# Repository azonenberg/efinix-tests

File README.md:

# efinix-tests
Miscellaneous experiments with Efinix FPGAs

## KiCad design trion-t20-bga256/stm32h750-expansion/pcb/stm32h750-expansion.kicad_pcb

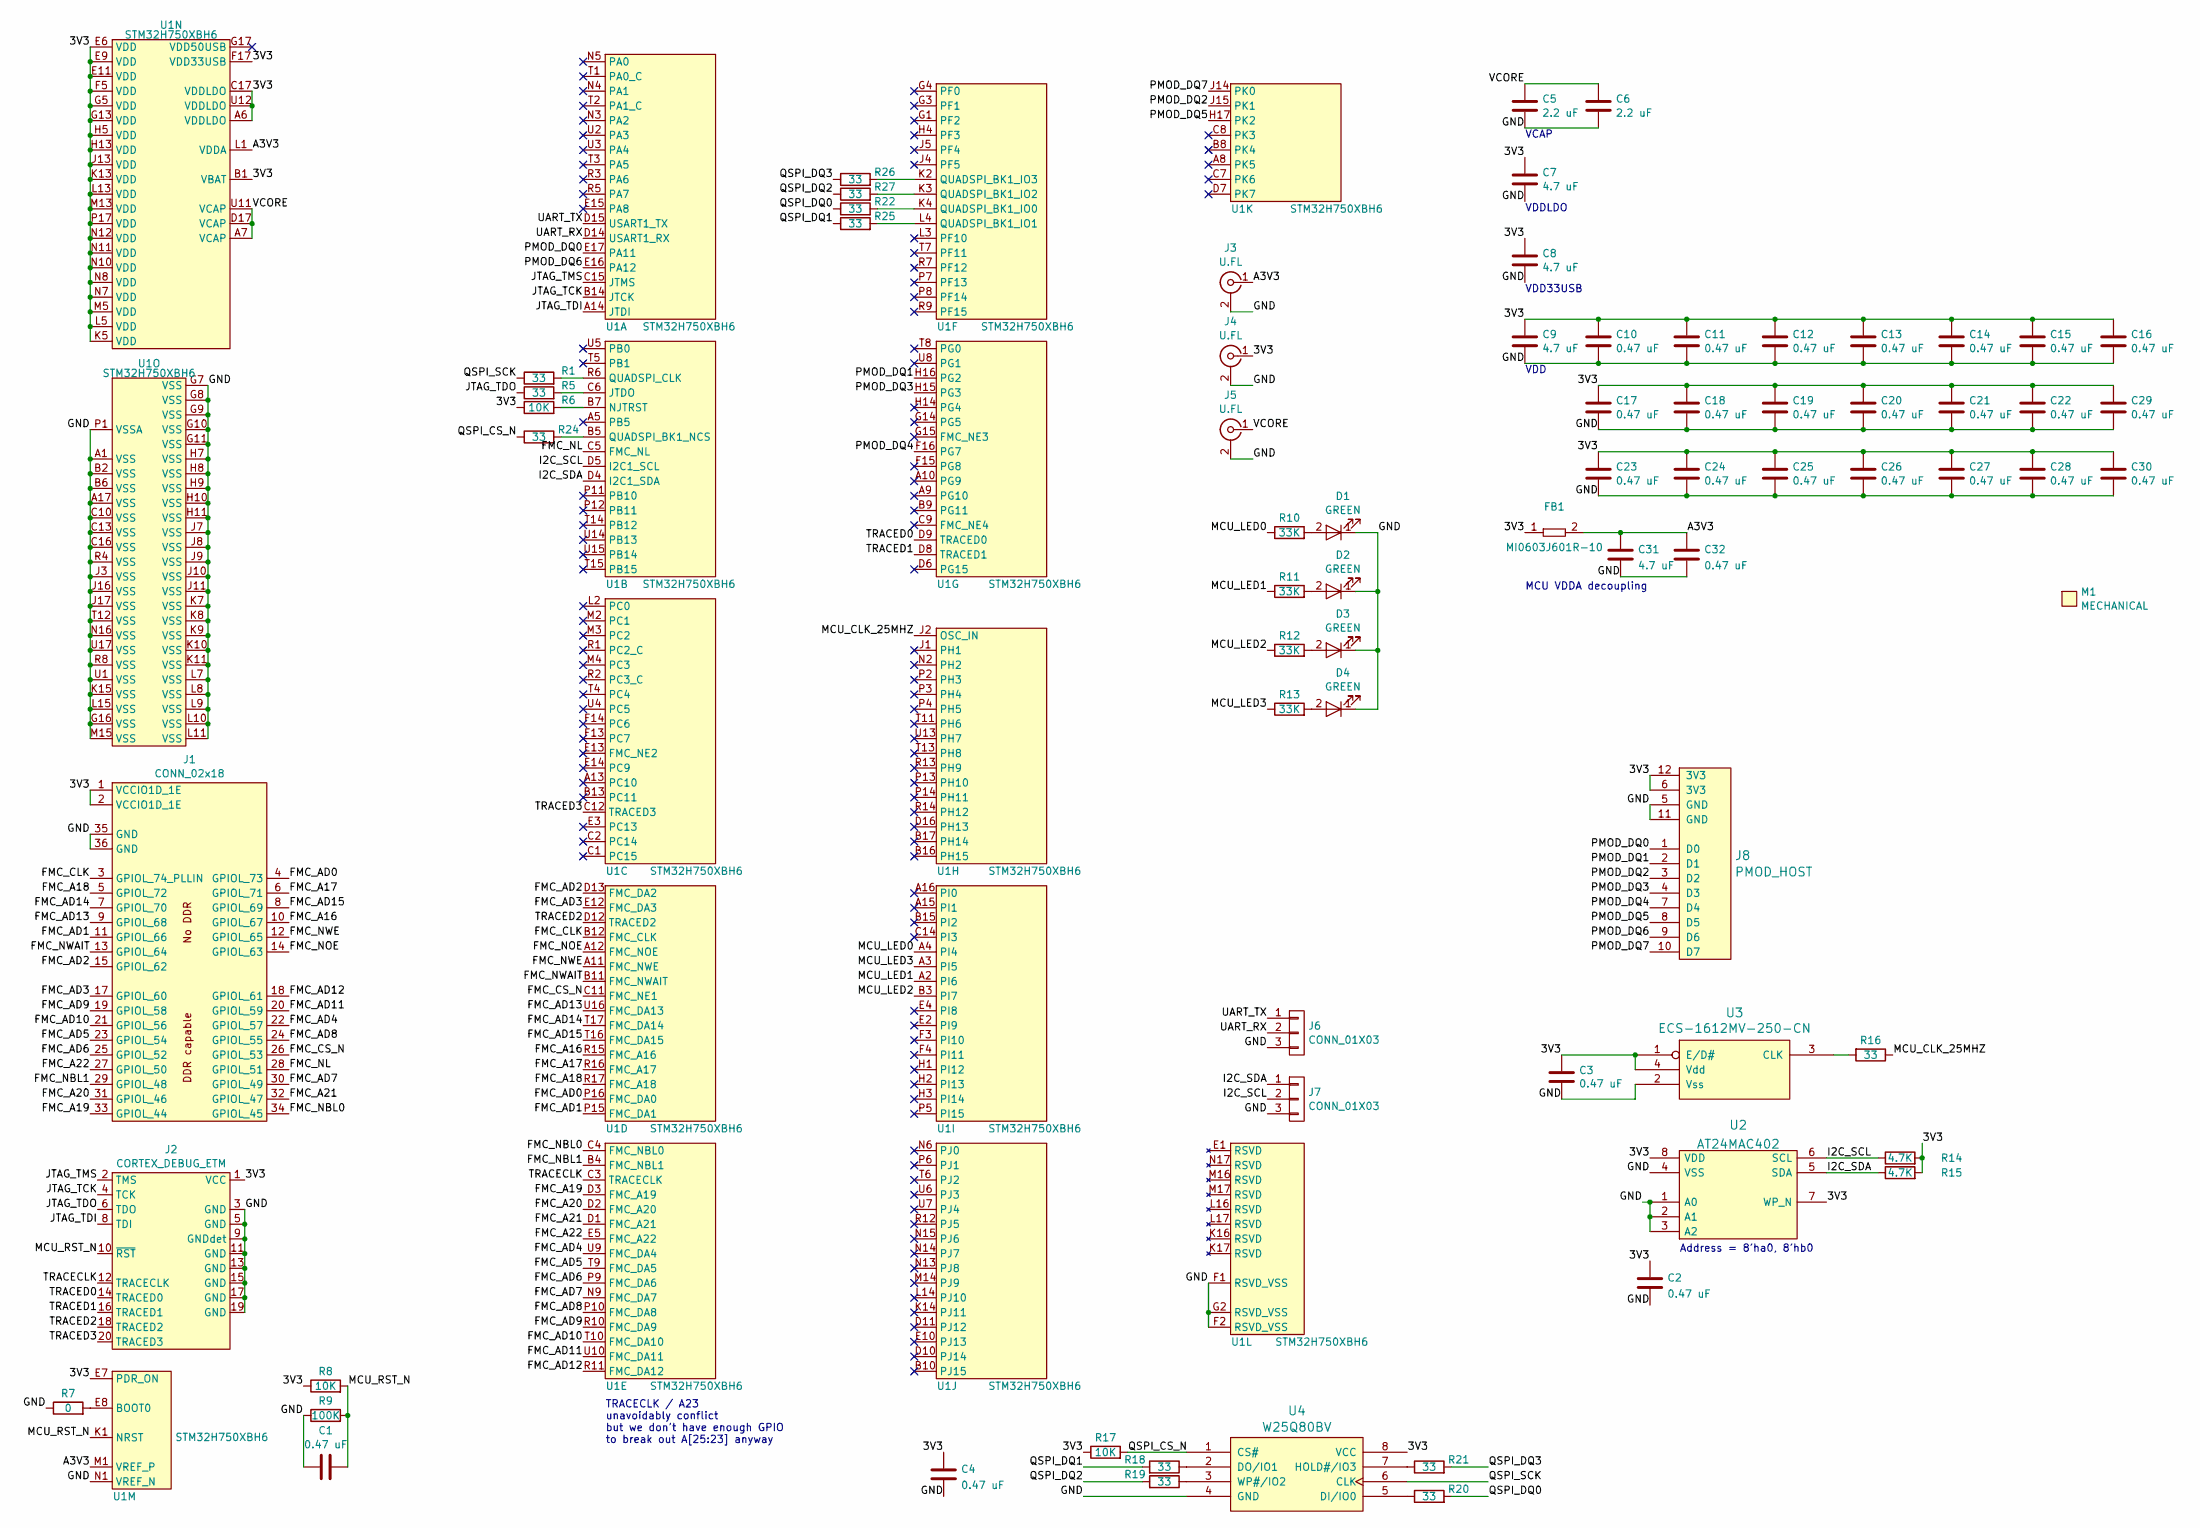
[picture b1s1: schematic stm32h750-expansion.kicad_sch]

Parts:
C1, C2, C3, C4, C10, C11, C12, C13, C14, C15, C16, C17, C18, C19, C20, C21, C22, C23, C24, C25, C26, C27, C28, C29, C30, C32: 0.47 uF; EIA_0402_CAP_NOSILK
C5, C6: 2.2 uF; EIA_0603_CAP_NOSILK
C7, C8, C9, C31: 4.7 uF; EIA_0603_CAP_NOSILK
D1, D2, D3, D4: GREEN; EIA_0402_LED
FB1: MI0603J601R-10; EIA_0603_INDUCTOR_NOSILK
J1: CONN_02x18; CONN_HEADER_2.54MM_2x18_FEMALE
J2: CORTEX_DEBUG_ETM; CONN_HEADER_1.27MM_2x10_SMT_SAMTEC_FTSH-110-01-L-DV-K
J3, J4, J5: U.FL; CONN_U.FL_TE_1909763-1
J6, J7: CONN_01X03; CONN_HEADER_2.54MM_1x3_REFLOW
J8: PMOD_HOST; CONN_HEADER_2.54MM_2x6_RA_PMOD_HOST
M1: MECHANICAL; LONGTHING-1200DPI
R1, R5, R16, R18, R19, R20, R21, R22, R24, R25, R26, R27: 33; EIA_0402_RES_NOSILK
R6, R8, R17: 10K; EIA_0402_RES_NOSILK
R7: 0; EIA_0402_RES_NOSILK
R9: 100K; EIA_0402_RES_NOSILK
R10, R11, R12, R13: 33K; EIA_0402_RES_NOSILK
R14, R15: 4.7K; EIA_0402_RES_NOSILK
U1: STM32H750XBH6; BGA_265_14x14_DEPOP_0.8MM
U2: AT24MAC402; DFN_8_0.5MM_2x3MM_TALL
U3: ECS-1612MV-250-CN; OSCILLATOR_1.6x1.2
U4: W25Q80BV; SOIC_8_5.3MM

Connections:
/3V3: C2.1, C3.1, C4.1, C7.1, C8.1, C9.1, C10.1, C11.1, C12.1, C13.1, C14.1, C15.1, C16.1, C17.1, C18.1, C19.1, C20.1, C21.1, C22.1, C23.1, C24.1, C25.1, C26.1, C27.1, C28.1, C29.1, C30.1, FB1.1, J1.1 (VCCIO1D_1E), J1.2 (VCCIO1D_1E), J2.1 (VCC), J4.1 (In), J8.6 (3V3), J8.12 (3V3), R6.1, R8.1, R14.2, R15.2, R17.1, U1.A6 (VDDLDO), U1.B1 (VBAT), U1.C17 (VDDLDO), U1.E6 (VDD), U1.E7 (PDR_ON), U1.E9 (VDD), U1.E11 (VDD), U1.F5 (VDD), U1.F17 (VDD33USB), U1.G5 (VDD), U1.G13 (VDD), U1.H5 (VDD), U1.H13 (VDD), U1.J13 (VDD), U1.K5 (VDD), U1.K13 (VDD), U1.L5 (VDD), U1.L13 (VDD), U1.M5 (VDD), U1.M13 (VDD), U1.N7 (VDD), U1.N8 (VDD), U1.N10 (VDD), U1.N11 (VDD), U1.N12 (VDD), U1.P17 (VDD), U1.U12 (VDDLDO), U2.7 (WP_N), U2.8 (VDD), U3.1 (E/D#), U3.4 (Vdd), U4.8 (VCC)
/A3V3: C31.1, C32.1, FB1.2, J3.1 (In), U1.L1 (VDDA), U1.M1 (VREF_P)
/FMC_A16: J1.10 (GPIOL_67), U1.R15 (FMC_A16)
/FMC_A17: J1.6 (GPIOL_71), U1.R16 (FMC_A17)
/FMC_A18: J1.5 (GPIOL_72), U1.R17 (FMC_A18)
/FMC_A19: J1.33 (GPIOL_44), U1.D3 (FMC_A19)
/FMC_A20: J1.31 (GPIOL_46), U1.D2 (FMC_A20)
/FMC_A21: J1.32 (GPIOL_47), U1.D1 (FMC_A21)
/FMC_A22: J1.27 (GPIOL_50), U1.E5 (FMC_A22)
/FMC_AD0: J1.4 (GPIOL_73), U1.P16 (FMC_DA0)
/FMC_AD1: J1.11 (GPIOL_66), U1.P15 (FMC_DA1)
/FMC_AD2: J1.15 (GPIOL_62), U1.D13 (FMC_DA2)
/FMC_AD3: J1.17 (GPIOL_60), U1.E12 (FMC_DA3)
/FMC_AD4: J1.22 (GPIOL_57), U1.U9 (FMC_DA4)
/FMC_AD5: J1.23 (GPIOL_54), U1.T9 (FMC_DA5)
/FMC_AD6: J1.25 (GPIOL_52), U1.P9 (FMC_DA6)
/FMC_AD7: J1.30 (GPIOL_49), U1.N9 (FMC_DA7)
/FMC_AD8: J1.24 (GPIOL_55), U1.P10 (FMC_DA8)
/FMC_AD9: J1.19 (GPIOL_58), U1.R10 (FMC_DA9)
/FMC_AD10: J1.21 (GPIOL_56), U1.T10 (FMC_DA10)
/FMC_AD11: J1.20 (GPIOL_59), U1.U10 (FMC_DA11)
/FMC_AD12: J1.18 (GPIOL_61), U1.R11 (FMC_DA12)
/FMC_AD13: J1.9 (GPIOL_68), U1.U16 (FMC_DA13)
/FMC_AD14: J1.7 (GPIOL_70), U1.T17 (FMC_DA14)
/FMC_AD15: J1.8 (GPIOL_69), U1.T16 (FMC_DA15)
/FMC_CLK: J1.3 (GPIOL_74_PLLIN), U1.B12 (FMC_CLK)
/FMC_CS_N: J1.26 (GPIOL_53), U1.C11 (FMC_NE1)
/FMC_NBL0: J1.34 (GPIOL_45), U1.C4 (FMC_NBL0)
/FMC_NBL1: J1.29 (GPIOL_48), U1.B4 (FMC_NBL1)
/FMC_NL: J1.28 (GPIOL_51), U1.C5 (FMC_NL)
/FMC_NOE: J1.14 (GPIOL_63), U1.A12 (FMC_NOE)
/FMC_NWAIT: J1.13 (GPIOL_64), U1.B11 (FMC_NWAIT)
/FMC_NWE: J1.12 (GPIOL_65), U1.A11 (FMC_NWE)
/GND: C1.1, C2.2, C3.2, C4.2, C5.2, C6.2, C7.2, C8.2, C9.2, C10.2, C11.2, C12.2, C13.2, C14.2, C15.2, C16.2, C17.2, C18.2, C19.2, C20.2, C21.2, C22.2, C23.2, C24.2, C25.2, C26.2, C27.2, C28.2, C29.2, C30.2, C31.2, C32.2, D1.1 (K), D2.1 (K), D3.1 (K), D4.1 (K), J1.35 (GND), J1.36 (GND), J2.3 (GND), J2.5 (GND), J2.9 (GNDdet), J2.11 (GND), J2.13 (GND), J2.15 (GND), J2.17 (GND), J2.19 (GND), J3.2 (Ext), J4.2 (Ext), J5.2 (Ext), J6.3, J7.3, J8.5 (GND), J8.11 (GND), R7.1, R9.1, U1.A1 (VSS), U1.A17 (VSS), U1.B2 (VSS), U1.B6 (VSS), U1.C10 (VSS), U1.C13 (VSS), U1.C16 (VSS), U1.F1 (RSVD_VSS), U1.F2 (RSVD_VSS), U1.G2 (RSVD_VSS), U1.G7 (VSS), U1.G8 (VSS), U1.G9 (VSS), U1.G10 (VSS), U1.G11 (VSS), U1.G16 (VSS), U1.H7 (VSS), U1.H8 (VSS), U1.H9 (VSS), U1.H10 (VSS), U1.H11 (VSS), U1.J3 (VSS), U1.J7 (VSS), U1.J8 (VSS), U1.J9 (VSS), U1.J10 (VSS), U1.J11 (VSS), U1.J16 (VSS), U1.J17 (VSS), U1.K7 (VSS), U1.K8 (VSS), U1.K9 (VSS), U1.K10 (VSS), U1.K11 (VSS), U1.K15 (VSS), U1.L7 (VSS), U1.L8 (VSS), U1.L9 (VSS), U1.L10 (VSS), U1.L11 (VSS), U1.L15 (VSS), U1.M15 (VSS), U1.N1 (VREF_N), U1.N16 (VSS), U1.P1 (VSSA), U1.R4 (VSS), U1.R8 (VSS), U1.T12 (VSS), U1.U1 (VSS), U1.U17 (VSS), U2.1 (A0), U2.2 (A1), U2.3 (A2), U2.4 (VSS), U3.2 (Vss), U4.4 (GND)
/I2C_SCL: J7.2, R14.1, U1.D5 (I2C1_SCL), U2.6 (SCL)
/I2C_SDA: J7.1, R15.1, U1.D4 (I2C1_SDA), U2.5 (SDA)
/JTAG_TCK: J2.4 (TCK), U1.B14 (JTCK)
/JTAG_TDI: J2.8 (TDI), U1.A14 (JTDI)
/JTAG_TDO: J2.6 (TDO), R5.1
/JTAG_TMS: J2.2 (TMS), U1.C15 (JTMS)
/MCU_CLK_25MHZ: R16.1, U1.J2 (OSC_IN)
/MCU_LED0: R10.1, U1.A4 (PI4)
/MCU_LED1: R11.1, U1.A2 (PI6)
/MCU_LED2: R12.1, U1.B3 (PI7)
/MCU_LED3: R13.1, U1.A3 (PI5)
/MCU_RST_N: C1.2, J2.10 (~RST), R8.2, R9.2, U1.K1 (NRST)
/PMOD_DQ0: J8.1 (D0), U1.E17 (PA11)
/PMOD_DQ1: J8.2 (D1), U1.H16 (PG2)
/PMOD_DQ2: J8.3 (D2), U1.J15 (PK1)
/PMOD_DQ3: J8.4 (D3), U1.H15 (PG3)
/PMOD_DQ4: J8.7 (D4), U1.F16 (PG7)
/PMOD_DQ5: J8.8 (D5), U1.H17 (PK2)
/PMOD_DQ6: J8.9 (D6), U1.E16 (PA12)
/PMOD_DQ7: J8.10 (D7), U1.J14 (PK0)
/QSPI_CS_N: R17.2, R24.1, U4.1 (CS#)
/QSPI_DQ0: R20.2, R22.1
/QSPI_DQ1: R18.2, R25.1
/QSPI_DQ2: R19.2, R27.1
/QSPI_DQ3: R21.2, R26.1
/QSPI_SCK: R1.1, U4.6 (CLK)
/TRACECLK: J2.12 (TRACECLK), U1.C3 (TRACECLK)
/TRACED0: J2.14 (TRACED0), U1.D9 (TRACED0)
/TRACED1: J2.16 (TRACED1), U1.D8 (TRACED1)
/TRACED2: J2.18 (TRACED2), U1.D12 (TRACED2)
/TRACED3: J2.20 (TRACED3), U1.C12 (TRACED3)
/UART_RX: J6.2, U1.D14 (USART1_RX)
/UART_TX: J6.1, U1.D15 (USART1_TX)
/VCORE: C5.1, C6.1, J5.1 (In), U1.A7 (VCAP), U1.D17 (VCAP), U1.U11 (VCAP)
unnamed: D1.2 (A), R10.2
unnamed: D2.2 (A), R11.2
unnamed: D3.2 (A), R12.2
unnamed: D4.2 (A), R13.2
unnamed: R1.2, U1.R6 (QUADSPI_CLK)
unnamed: R5.2, U1.C6 (JTDO)
unnamed: R6.2, U1.B7 (NJTRST)
unnamed: R24.2, U1.B5 (QUADSPI_BK1_NCS)
unnamed: R26.2, U1.K2 (QUADSPI_BK1_IO3)
unnamed: R27.2, U1.K3 (QUADSPI_BK1_IO2)
unnamed: R22.2, U1.K4 (QUADSPI_BK1_IO0)
unnamed: R25.2, U1.L4 (QUADSPI_BK1_IO1)
unnamed: R7.2, U1.E8 (BOOT0)
unnamed: R16.2, U3.3 (CLK)
unnamed: R20.1, U4.5 (DI/IO0)
unnamed: R18.1, U4.2 (DO/IO1)
unnamed: R21.1, U4.7 (HOLD#/IO3)
unnamed: R19.1, U4.3 (WP#/IO2)

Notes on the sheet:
Address = 8'ha0, 8'hb0
TRACECLK / A23 unavoidably conflict but we don't have enough GPIO to break out A[25:23] anyway
VDD33USB
MCU VDDA decoupling
VDDLDO
VCAP
VDD

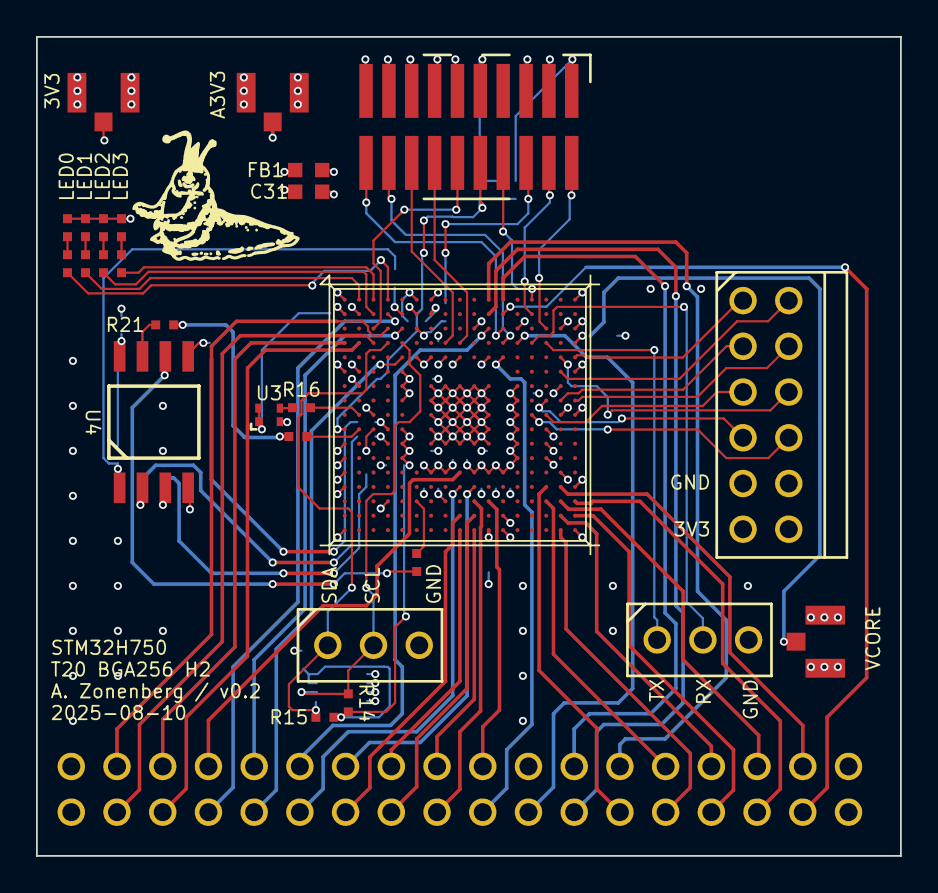
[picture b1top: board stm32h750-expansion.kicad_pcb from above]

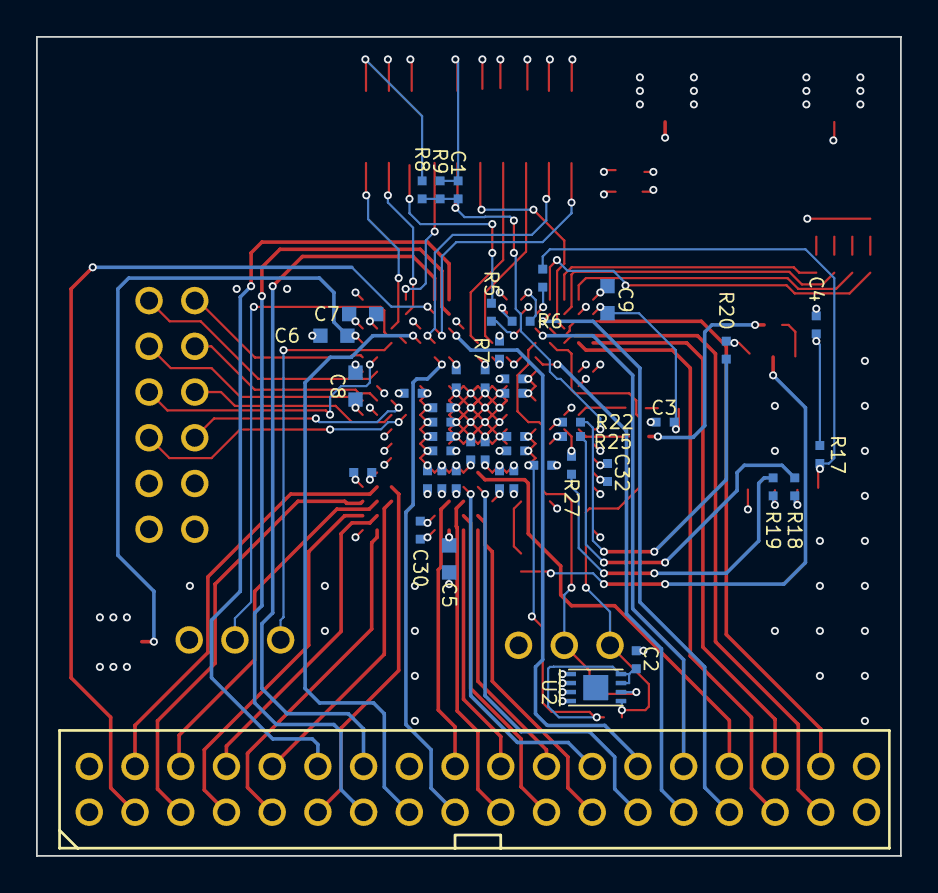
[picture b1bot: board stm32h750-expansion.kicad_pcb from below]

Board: 4 copper layers, 48.0 x 45.5 mm, 73 parts (46 on the bottom side), 86 nets.

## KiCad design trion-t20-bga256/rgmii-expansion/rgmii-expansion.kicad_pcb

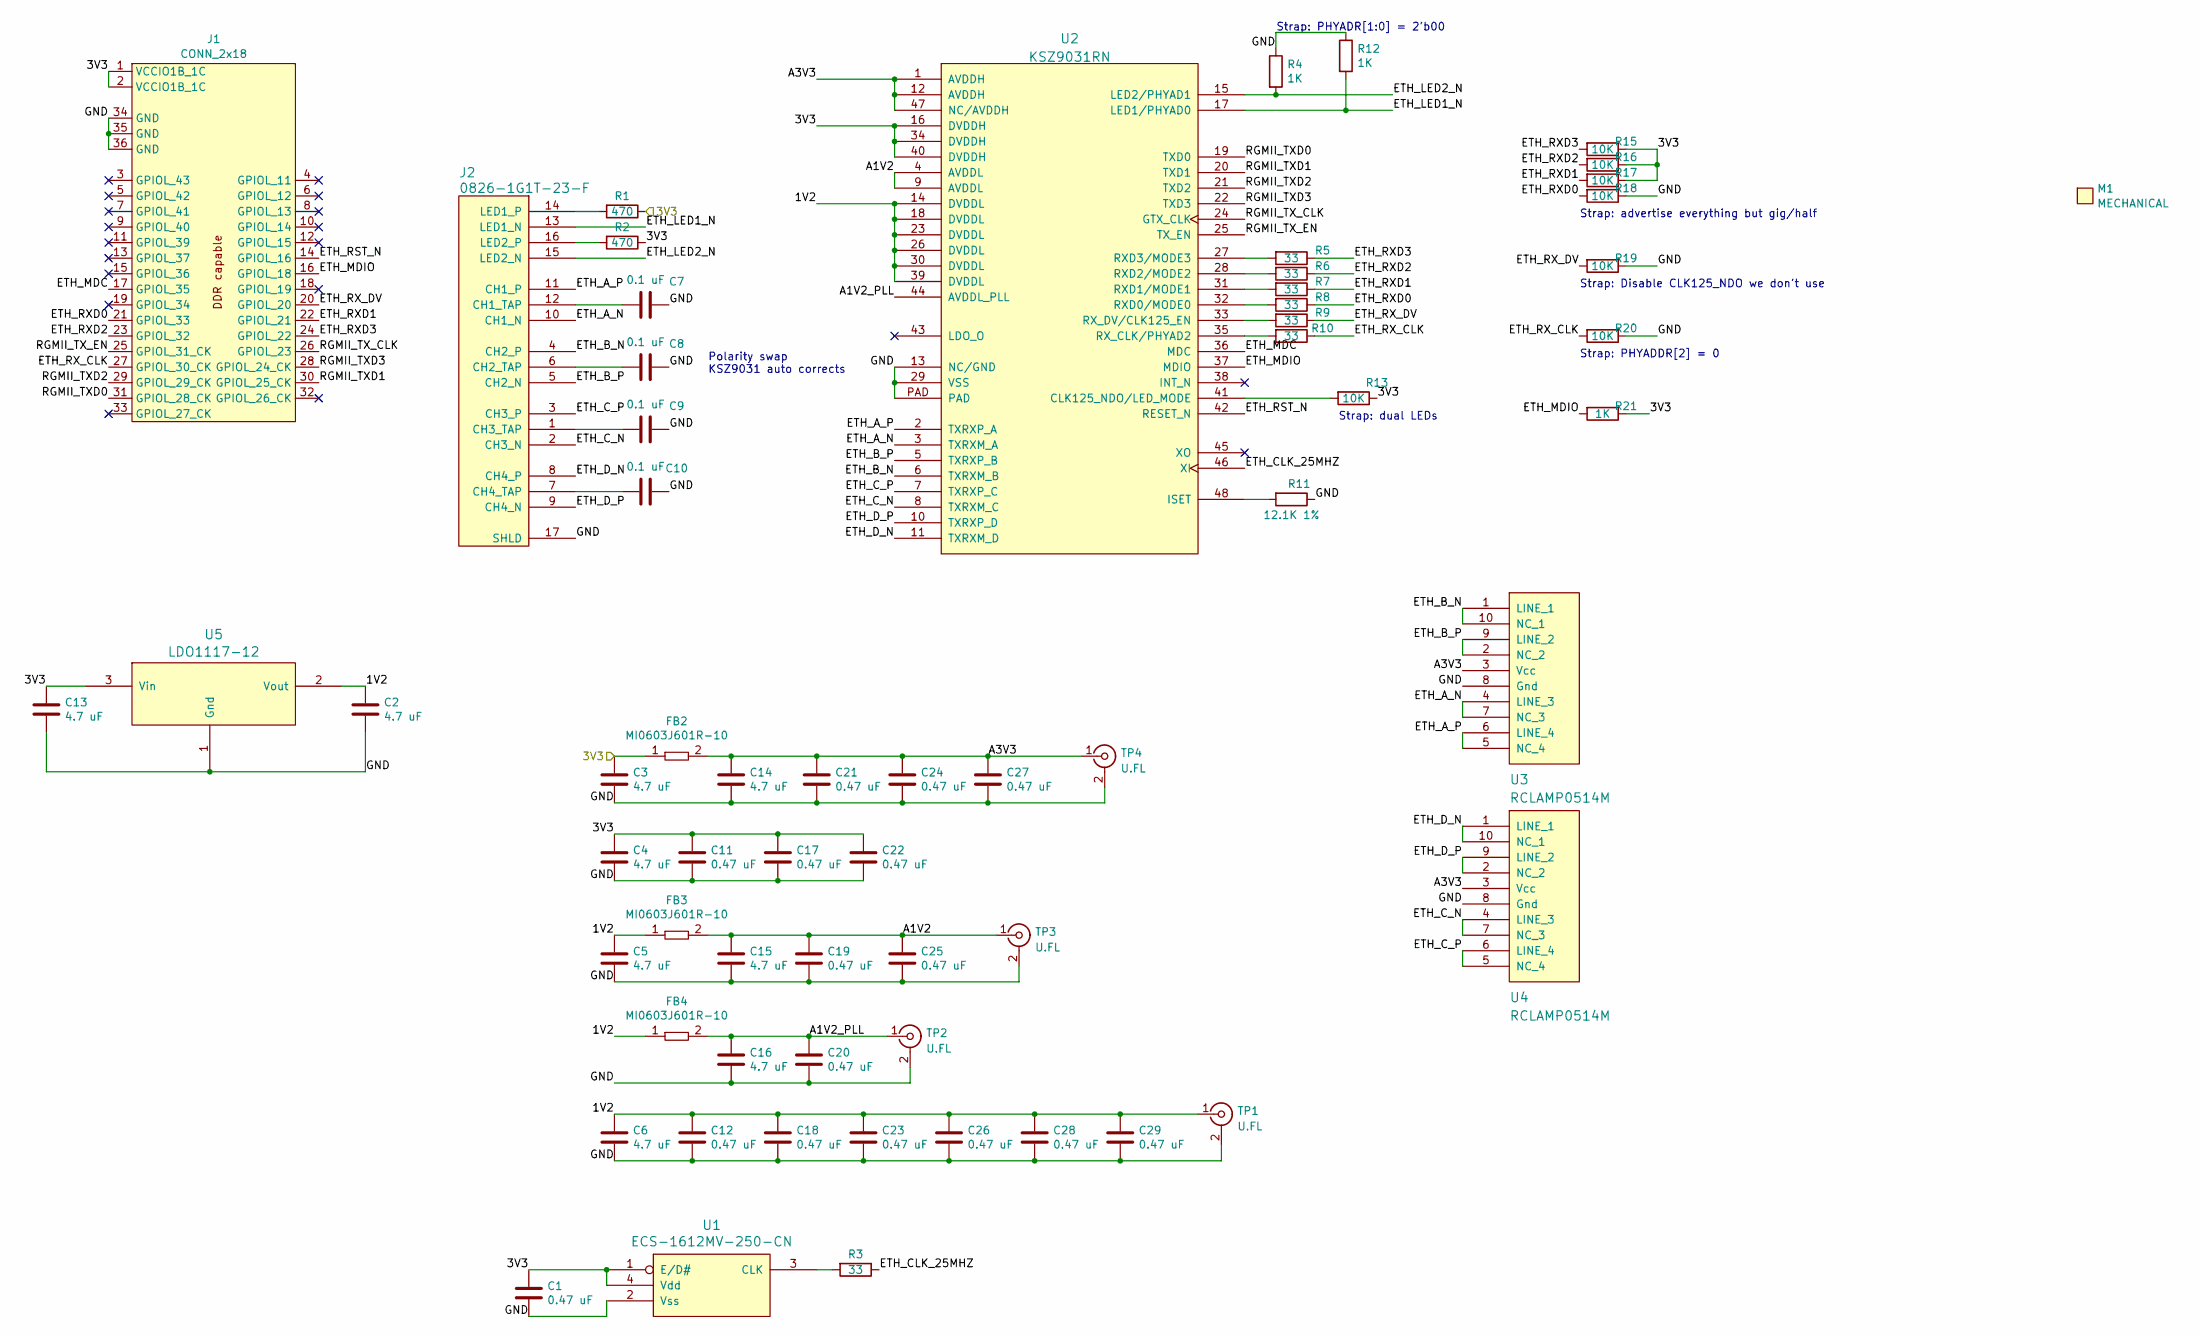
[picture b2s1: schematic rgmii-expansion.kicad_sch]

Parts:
C1, C11, C12, C17, C18, C19, C20, C21, C22, C23, C24, C25, C26, C27, C28, C29: 0.47 uF; EIA_0402_CAP_NOSILK
C2, C3, C4, C5, C6, C13, C14, C15, C16: 4.7 uF; EIA_0603_CAP_NOSILK
C7, C8, C9, C10: 0.1 uF; EIA_0402_CAP_NOSILK
FB2, FB3, FB4: MI0603J601R-10; EIA_0603_INDUCTOR_NOSILK
J1: CONN_2x18; CONN_HEADER_2.54MM_2x18_FEMALE
J2: 0826-1G1T-23-F; CONN_BELFUSE_0826_1G1T_23_F
M1: MECHANICAL; LONGTHING-600DPI
R1, R2: 470; EIA_0402_RES_NOSILK
R3, R5, R6, R7, R8, R9, R10: 33; EIA_0402_RES_NOSILK
R4, R12, R21: 1K; EIA_0402_RES_NOSILK
R11: 12.1K 1%; EIA_0402_RES_NOSILK
R13, R15, R16, R17, R18, R19, R20: 10K; EIA_0402_RES_NOSILK
TP1, TP2, TP3, TP4: U.FL; CONN_U.FL_TE_1909763-1
U1: ECS-1612MV-250-CN; OSCILLATOR_1.6x1.2
U2: KSZ9031RN; QFN_48_0.5MM_7x7MM
U3, U4: RCLAMP0514M; SOP_10_0.5MM_3MM
U5: LDO1117-12; SOT223-4

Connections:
/1V2: C2.1, C5.1, C6.1, C12.1, C18.1, C23.1, C26.1, C28.1, C29.1, FB3.1, FB4.1, TP1.1 (In), U2.14 (DVDDL), U2.18 (DVDDL), U2.23 (DVDDL), U2.26 (DVDDL), U2.30 (DVDDL), U2.39 (DVDDL), U5.2 (Vout)
/3V3: C1.1, C3.1, C4.1, C11.1, C13.1, C17.1, C22.1, FB2.1, J1.1 (VCCIO1B_1C), J1.2 (VCCIO1B_1C), R1.1, R2.1, R13.1, R15.1, R16.1, R17.1, R21.1, U1.1 (E/D#), U1.4 (Vdd), U2.16 (DVDDH), U2.34 (DVDDH), U2.40 (DVDDH), U5.3 (Vin)
/A1V2: C15.1, C19.1, C25.1, FB3.2, TP3.1 (In), U2.4 (AVDDL), U2.9 (AVDDL)
/A1V2_PLL: C16.1, C20.1, FB4.2, TP2.1 (In), U2.44 (AVDDL_PLL)
/A3V3: C14.1, C21.1, C24.1, C27.1, FB2.2, TP4.1 (In), U2.1 (AVDDH), U2.12 (AVDDH), U2.47 (NC/AVDDH), U3.3 (Vcc), U4.3 (Vcc)
/ETH_A_N: J2.10 (CH1_N), U2.3 (TXRXM_A), U3.4 (LINE_3), U3.7 (NC_3)
/ETH_A_P: J2.11 (CH1_P), U2.2 (TXRXP_A), U3.5 (NC_4), U3.6 (LINE_4)
/ETH_B_N: J2.4 (CH2_P), U2.6 (TXRXM_B), U3.1 (LINE_1), U3.10 (NC_1)
/ETH_B_P: J2.5 (CH2_N), U2.5 (TXRXP_B), U3.2 (NC_2), U3.9 (LINE_2)
/ETH_CLK_25MHZ: R3.1, U2.46 (XI)
/ETH_C_N: J2.2 (CH3_N), U2.8 (TXRXM_C), U4.4 (LINE_3), U4.7 (NC_3)
/ETH_C_P: J2.3 (CH3_P), U2.7 (TXRXP_C), U4.5 (NC_4), U4.6 (LINE_4)
/ETH_D_N: J2.8 (CH4_P), U2.11 (TXRXM_D), U4.1 (LINE_1), U4.10 (NC_1)
/ETH_D_P: J2.9 (CH4_N), U2.10 (TXRXP_D), U4.2 (NC_2), U4.9 (LINE_2)
/ETH_LED1_N: J2.13 (LED1_N), R12.2, U2.17 (LED1/PHYAD0)
/ETH_LED2_N: J2.15 (LED2_N), R4.2, U2.15 (LED2/PHYAD1)
/ETH_MDC: J1.17 (GPIOL_35), U2.36 (MDC)
/ETH_MDIO: J1.16 (GPIOL_18), R21.2, U2.37 (MDIO)
/ETH_RST_N: J1.14 (GPIOL_16), U2.42 (RESET_N)
/ETH_RXD0: J1.21 (GPIOL_33), R8.1, R18.2
/ETH_RXD1: J1.22 (GPIOL_21), R7.1, R17.2
/ETH_RXD2: J1.23 (GPIOL_32), R6.1, R16.2
/ETH_RXD3: J1.24 (GPIOL_22), R5.1, R15.2
/ETH_RX_CLK: J1.27 (GPIOL_30_CK), R10.1, R20.2
/ETH_RX_DV: J1.20 (GPIOL_20), R9.1, R19.2
/GND: C1.2, C2.2, C3.2, C4.2, C5.2, C6.2, C7.1, C8.1, C9.1, C10.1, C11.2, C12.2, C13.2, C14.2, C15.2, C16.2, C17.2, C18.2, C19.2, C20.2, C21.2, C22.2, C23.2, C24.2, C25.2, C26.2, C27.2, C28.2, C29.2, J1.34 (GND), J1.35 (GND), J1.36 (GND), J2.17 (SHLD), R4.1, R11.1, R12.1, R18.1, R19.1, R20.1, TP1.2 (Ext), TP2.2 (Ext), TP3.2 (Ext), TP4.2 (Ext), U1.2 (Vss), U2.13 (NC/GND), U2.29 (VSS), U2.PAD, U3.8 (Gnd), U4.8 (Gnd), U5.1 (Gnd)
/RGMII_TXD0: J1.31 (GPIOL_28_CK), U2.19 (TXD0)
/RGMII_TXD1: J1.30 (GPIOL_25_CK), U2.20 (TXD1)
/RGMII_TXD2: J1.29 (GPIOL_29_CK), U2.21 (TXD2)
/RGMII_TXD3: J1.28 (GPIOL_24_CK), U2.22 (TXD3)
/RGMII_TX_CLK: J1.26 (GPIOL_23), U2.24 (GTX_CLK)
/RGMII_TX_EN: J1.25 (GPIOL_31_CK), U2.25 (TX_EN)
unnamed: C7.2, J2.12 (CH1_TAP)
unnamed: C8.2, J2.6 (CH2_TAP)
unnamed: C9.2, J2.1 (CH3_TAP)
unnamed: C10.2, J2.7 (CH4_TAP)
unnamed: J2.14 (LED1_P), R1.2
unnamed: J2.16 (LED2_P), R2.2
unnamed: R3.2, U1.3 (CLK)
unnamed: R13.2, U2.41 (CLK125_NDO/LED_MODE)
unnamed: R11.2, U2.48 (ISET)
unnamed: R8.2, U2.32 (RXD0/MODE0)
unnamed: R7.2, U2.31 (RXD1/MODE1)
unnamed: R6.2, U2.28 (RXD2/MODE2)
unnamed: R5.2, U2.27 (RXD3/MODE3)
unnamed: R10.2, U2.35 (RX_CLK/PHYAD2)
unnamed: R9.2, U2.33 (RX_DV/CLK125_EN)

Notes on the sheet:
Strap: PHYADR[1:0] = 2'b00
Strap: advertise everything but gig/half
Strap: Disable CLK125_NDO we don't use
Strap: PHYADDR[2] = 0
Strap: dual LEDs
Polarity swap KSZ9031 auto corrects

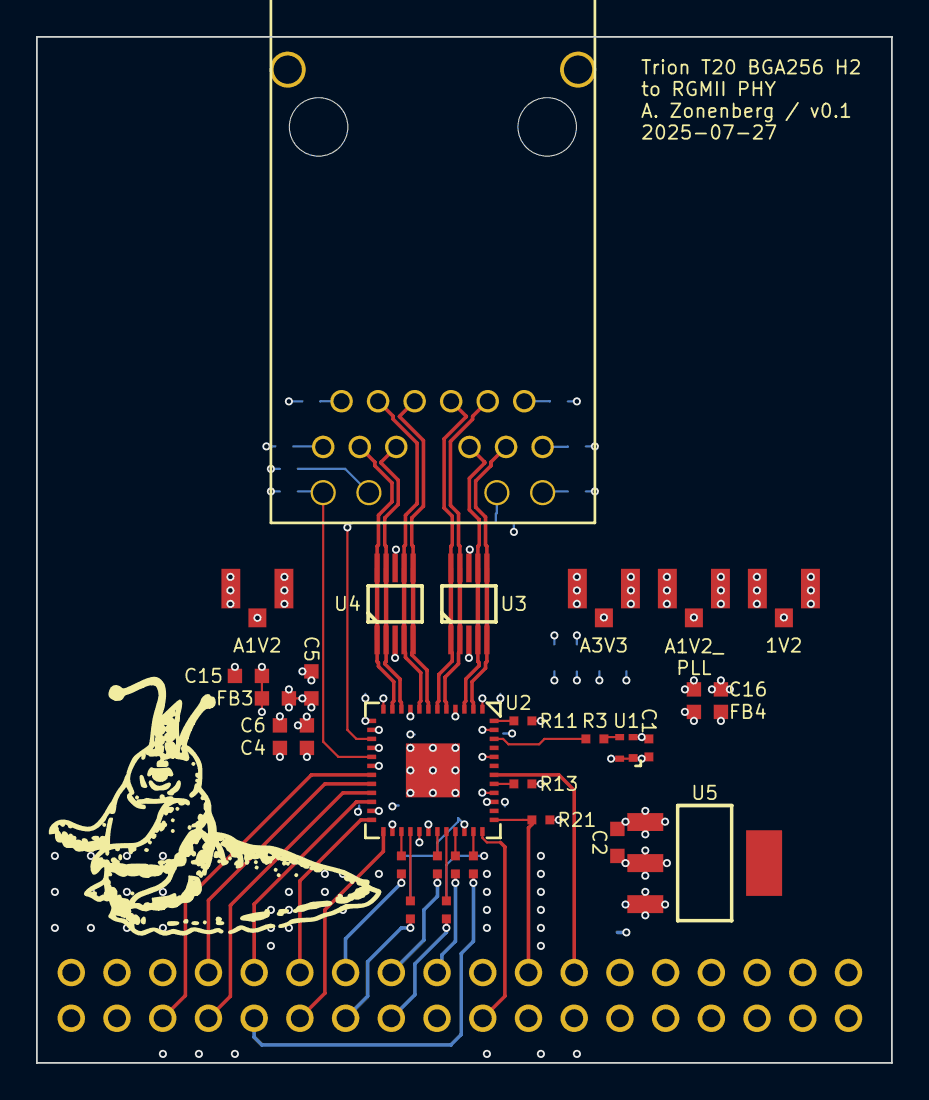
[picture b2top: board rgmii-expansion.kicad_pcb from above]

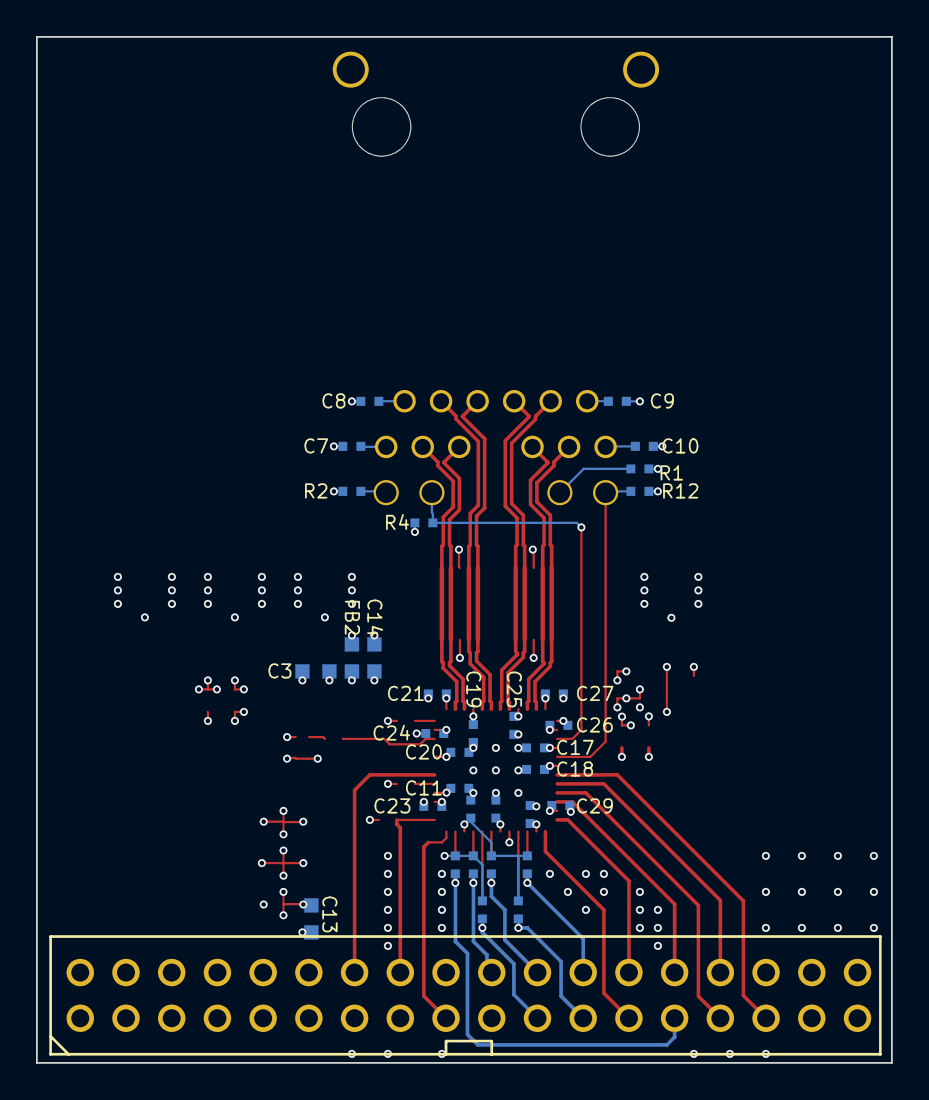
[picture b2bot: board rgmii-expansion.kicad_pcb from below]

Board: 4 copper layers, 47.5 x 57.0 mm, 64 parts (34 on the bottom side), 47 nets.

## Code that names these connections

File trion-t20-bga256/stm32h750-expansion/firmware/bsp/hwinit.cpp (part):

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{
	//Initialize the UART for local console: 115.2 Kbps using PA9 for UART1 transmit and PA10 for UART1 receive
	//TODO: nice interface for enabling UART interrupts
	static GPIOPin uart_tx(&GPIOA, 9, GPIOPin::MODE_PERIPHERAL, GPIOPin::SLEW_SLOW, 7);
	static GPIOPin uart_rx(&GPIOA, 10, GPIOPin::MODE_PERIPHERAL, GPIOPin::SLEW_SLOW, 7);

	//Enable the UART interrupt
	NVIC_EnableIRQ(37);
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	g_log("Initializing FMC...\n");
	LogIndenter li(g_log);

	static GPIOPin fmc_ad0(&GPIOD, 14, GPIOPin::MODE_PERIPHERAL, GPIOPin::SLEW_VERYFAST, 12);
	static GPIOPin fmc_ad1(&GPIOD, 15, GPIOPin::MODE_PERIPHERAL, GPIOPin::SLEW_VERYFAST, 12);
	static GPIOPin fmc_ad2(&GPIOD, 0, GPIOPin::MODE_PERIPHERAL, GPIOPin::SLEW_VERYFAST, 12);
	static GPIOPin fmc_ad3(&GPIOD, 1, GPIOPin::MODE_PERIPHERAL, GPIOPin::SLEW_VERYFAST, 12);
	static GPIOPin fmc_ad4(&GPIOE, 7, GPIOPin::MODE_PERIPHERAL, GPIOPin::SLEW_VERYFAST, 12);
	static GPIOPin fmc_ad5(&GPIOE, 8, GPIOPin::MODE_PERIPHERAL, GPIOPin::SLEW_VERYFAST, 12);
	static GPIOPin fmc_ad6(&GPIOE, 9, GPIOPin::MODE_PERIPHERAL, GPIOPin::SLEW_VERYFAST, 12);
	static GPIOPin fmc_ad7(&GPIOE, 10, GPIOPin::MODE_PERIPHERAL, GPIOPin::SLEW_VERYFAST, 12);
	static GPIOPin fmc_ad8(&GPIOE, 11, GPIOPin::MODE_PERIPHERAL, GPIOPin::SLEW_VERYFAST, 12);
	static GPIOPin fmc_ad9(&GPIOE, 12, GPIOPin::MODE_PERIPHERAL, GPIOPin::SLEW_VERYFAST, 12);
	static GPIOPin fmc_ad10(&GPIOE, 13, GPIOPin::MODE_PERIPHERAL, GPIOPin::SLEW_VERYFAST, 12);
	static GPIOPin fmc_ad11(&GPIOE, 14, GPIOPin::MODE_PERIPHERAL, GPIOPin::SLEW_VERYFAST, 12);
	static GPIOPin fmc_ad12(&GPIOE, 15, GPIOPin::MODE_PERIPHERAL, GPIOPin::SLEW_VERYFAST, 12);
	static GPIOPin fmc_ad13(&GPIOD, 8, GPIOPin::MODE_PERIPHERAL, GPIOPin::SLEW_VERYFAST, 12);
	static GPIOPin fmc_ad14(&GPIOD, 9, GPIOPin::MODE_PERIPHERAL, GPIOPin::SLEW_VERYFAST, 12);
	static GPIOPin fmc_ad15(&GPIOD, 10, GPIOPin::MODE_PERIPHERAL, GPIOPin::SLEW_VERYFAST, 12);

	static GPIOPin fmc_a16(&GPIOD, 11, GPIOPin::MODE_PERIPHERAL, GPIOPin::SLEW_VERYFAST, 12);
	static GPIOPin fmc_a17(&GPIOD, 12, GPIOPin::MODE_PERIPHERAL, GPIOPin::SLEW_VERYFAST, 12);
	static GPIOPin fmc_a18(&GPIOD, 13, GPIOPin::MODE_PERIPHERAL, GPIOPin::SLEW_VERYFAST, 12);
	static GPIOPin fmc_a19(&GPIOE, 3, GPIOPin::MODE_PERIPHERAL, GPIOPin::SLEW_VERYFAST, 12);
	static GPIOPin fmc_a20(&GPIOE, 4, GPIOPin::MODE_PERIPHERAL, GPIOPin::SLEW_VERYFAST, 12);
	static GPIOPin fmc_a21(&GPIOE, 5, GPIOPin::MODE_PERIPHERAL, GPIOPin::SLEW_VERYFAST, 12);
	static GPIOPin fmc_a22(&GPIOE, 6, GPIOPin::MODE_PERIPHERAL, GPIOPin::SLEW_VERYFAST, 12);
	//no A23...25 pinned out on this board
	//static GPIOPin fmc_a23(&GPIOE, 2, GPIOPin::MODE_PERIPHERAL, GPIOPin::SLEW_VERYFAST, FIXME);
	//static GPIOPin fmc_a24(&GPIOG, 13, GPIOPin::MODE_PERIPHERAL, GPIOPin::SLEW_VERYFAST, FIXME);
	//static GPIOPin fmc_a25(&GPIOG, 14, GPIOPin::MODE_PERIPHERAL, GPIOPin::SLEW_VERYFAST, FIXME);

	static GPIOPin fmc_nl_nadv(&GPIOB, 7, GPIOPin::MODE_PERIPHERAL, GPIOPin::SLEW_VERYFAST, 12);
	static GPIOPin fmc_nwait(&GPIOD, 6, GPIOPin::MODE_PERIPHERAL, GPIOPin::SLEW_VERYFAST, 12);
	static GPIOPin fmc_ne1(&GPIOD, 7, GPIOPin::MODE_PERIPHERAL, GPIOPin::SLEW_VERYFAST, 12);
	//static GPIOPin fmc_ne3(&GPIOG, 6, GPIOPin::MODE_PERIPHERAL, GPIOPin::SLEW_VERYFAST, FIXME);

	static GPIOPin fmc_clk(&GPIOD, 3, GPIOPin::MODE_PERIPHERAL, GPIOPin::SLEW_VERYFAST, 12);
	static GPIOPin fmc_noe(&GPIOD, 4, GPIOPin::MODE_PERIPHERAL, GPIOPin::SLEW_VERYFAST, 12);
	static GPIOPin fmc_nwe(&GPIOD, 5, GPIOPin::MODE_PERIPHERAL, GPIOPin::SLEW_VERYFAST, 12);
	static GPIOPin fmc_nbl0(&GPIOE, 0, GPIOPin::MODE_PERIPHERAL, GPIOPin::SLEW_VERYFAST, 12);
	static GPIOPin fmc_nbl1(&GPIOE, 1, GPIOPin::MODE_PERIPHERAL, GPIOPin::SLEW_VERYFAST, 12);

	//Add a pullup on NWAIT
	fmc_nwait.SetPullMode(GPIOPin::PULL_UP);

	InitFMCForFPGA();

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
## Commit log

2025-07-08 Initial version of blinky
2025-07-26 Initial version of stm32h750-expansion board
2025-07-26 Finished zone fill tweaks, ready to order
2025-07-26 Updated blinky test ignores and some debug things
2025-07-26 Updated final version of stm32h750-expansion with routing tweaks and export config
2025-07-27 Initial version of rgmii-expansion
2025-07-27 Updated rgmii-expansion with export config
2025-08-10 Updated stm32h750-expansion for v0.2
2025-09-01 Added standard submodules
2025-09-02 Initial test firmwar for h750 board
2025-09-02 Updated submodules
2025-09-03 Continued initial H750 bringup, now initializes FMC but nothing attached to it yet
2025-09-03 Initial FPGA test, no efx project here
2025-09-04 added efinity project, continued work on trion design
2025-09-04 Refactored PLL into its own module, time to blow away the efinity project again because it's horked
2025-09-04 Revert "Refactored PLL into its own module, time to blow away the efinity project again because it's horked"
    This reverts commit e62b9dea66cfc6a2d4a64bd007c2872ab18610ef.
2025-09-06 Initial quad spi test firmware
2025-09-07 Initial work on FPGA APB identification core etc
2025-09-07 Initial work on IDing trion. Reduced FMC interface speed to 62.5 MHz from 75 due to occasional instability
2025-09-07 Initial FPGA boot flash integration
2025-09-07 Began MDIO bringup
2025-09-07 More work on MDIO debug
2025-09-07 More attempts to debug tristate bus without any success
2025-09-07 New empty project with no pin constraints at all
2025-09-07 Added missing source files
2025-09-07 Fixed buggy tieoffs
2025-09-08 MDIO is now working
2025-09-08 Initial work on RGMII test
2026-06-30 Updated trion firmware from WIP
2026-06-30 Initial ti375 rtl harness
2026-06-30 Set up new efinity project for 1g serdes testing
2026-06-30 Continued VIO testing

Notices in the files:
trion-t20-bga256/stm32h750-expansion/firmware/bsp/hwinit.cpp:
Copyright (c) 2023-2025 Andrew D. Zonenberg and contributors
All rights reserved.
